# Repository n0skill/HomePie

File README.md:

HomePie
=======
Home automation using nordic semiconductor's NRF24L01+ modules

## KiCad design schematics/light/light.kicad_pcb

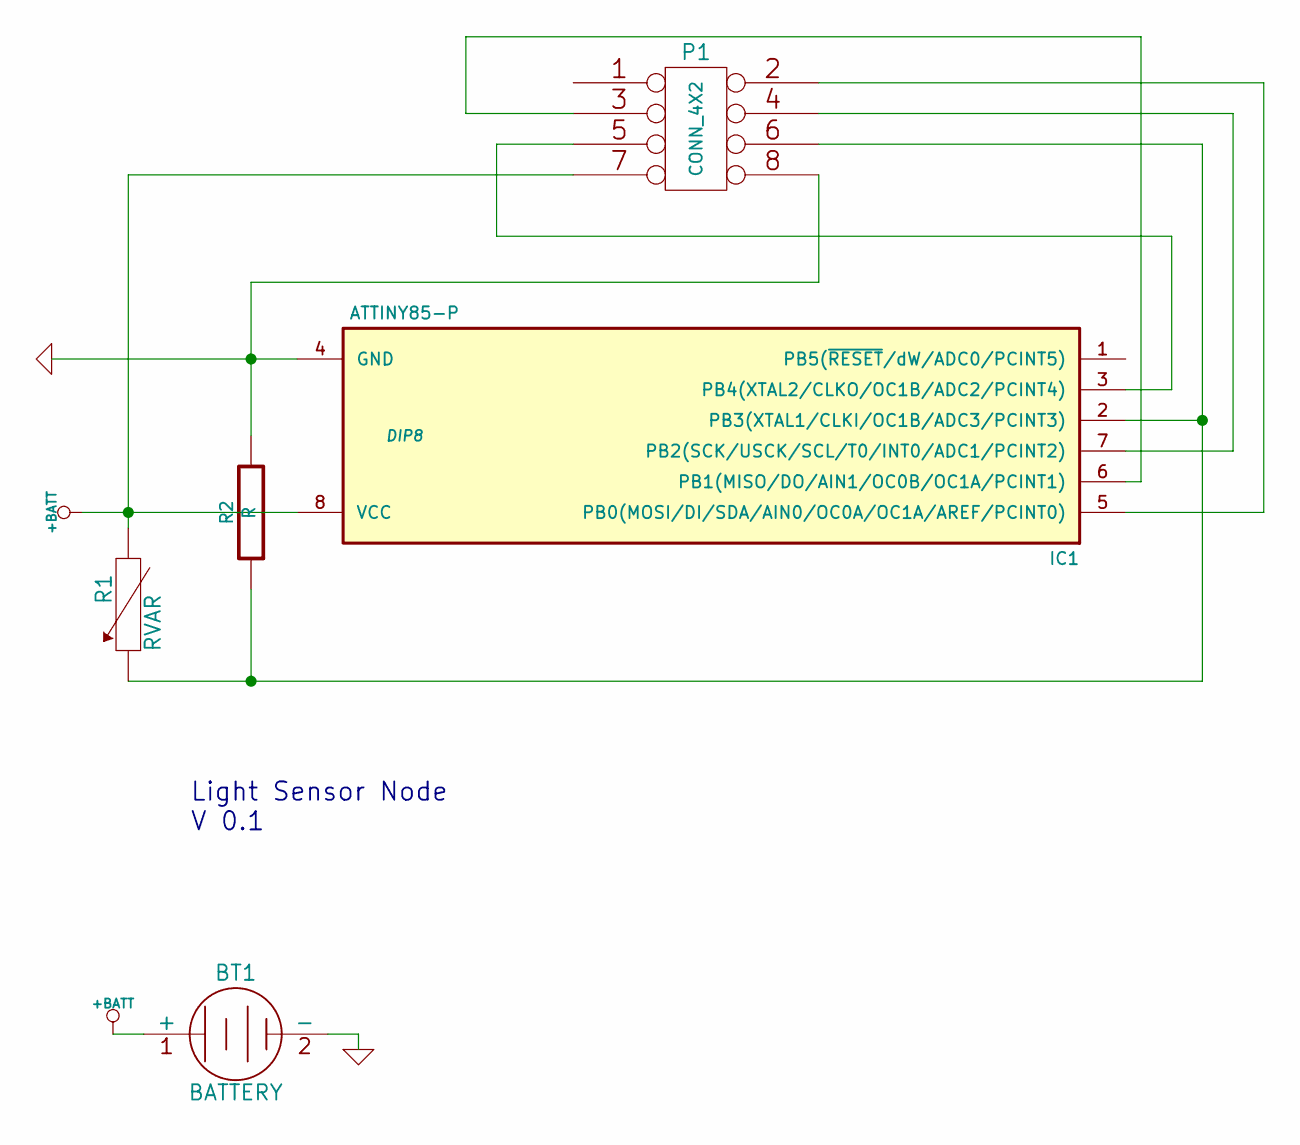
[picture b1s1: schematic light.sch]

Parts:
BT1: BATTERY
IC1: ATTINY85-P; DIP8
P1: CONN_4X2
R1: RVAR
R2: R

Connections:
+BATT: BT1.1 (+), IC1.8 (VCC), P1.7, R1.2
GND: BT1.2 (-), IC1.4 (GND), P1.8, R2.2
unnamed: IC1.6 (PB1(MISO/DO/AIN1/OC0B/OC1A/PCINT1)), P1.3
unnamed: IC1.3 (PB4(XTAL2/CLKO/OC1B/ADC2/PCINT4)), P1.5
unnamed: IC1.7 (PB2(SCK/USCK/SCL/T0/INT0/ADC1/PCINT2)), P1.4
unnamed: IC1.5 (PB0(MOSI/DI/SDA/AIN0/OC0A/OC1A/AREF/PCI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), P1.2
unnamed: IC1.2 (PB3(XTAL1/CLKI/OC1B/ADC3/PCINT3)), P1.6, R1.1, R2.1

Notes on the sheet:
Light Sensor Node V 0.1

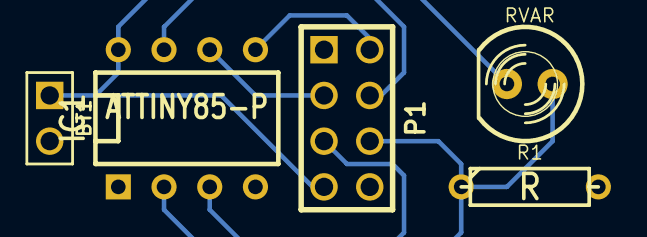
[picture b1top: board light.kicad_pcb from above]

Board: 2 copper layers, 5 parts (0 on the bottom side), 7 nets.

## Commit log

2015-10-04 Changed descripiton of the project
2015-10-04 Fix list of sensors update
2015-10-11 Update light sensor schematics
2015-10-11 Adds the setup.py script for easy installation
2015-10-15 Add rules class
2015-10-15 Add jsonfile class
2015-10-19 Add rules view in web interface. Fix some issues
